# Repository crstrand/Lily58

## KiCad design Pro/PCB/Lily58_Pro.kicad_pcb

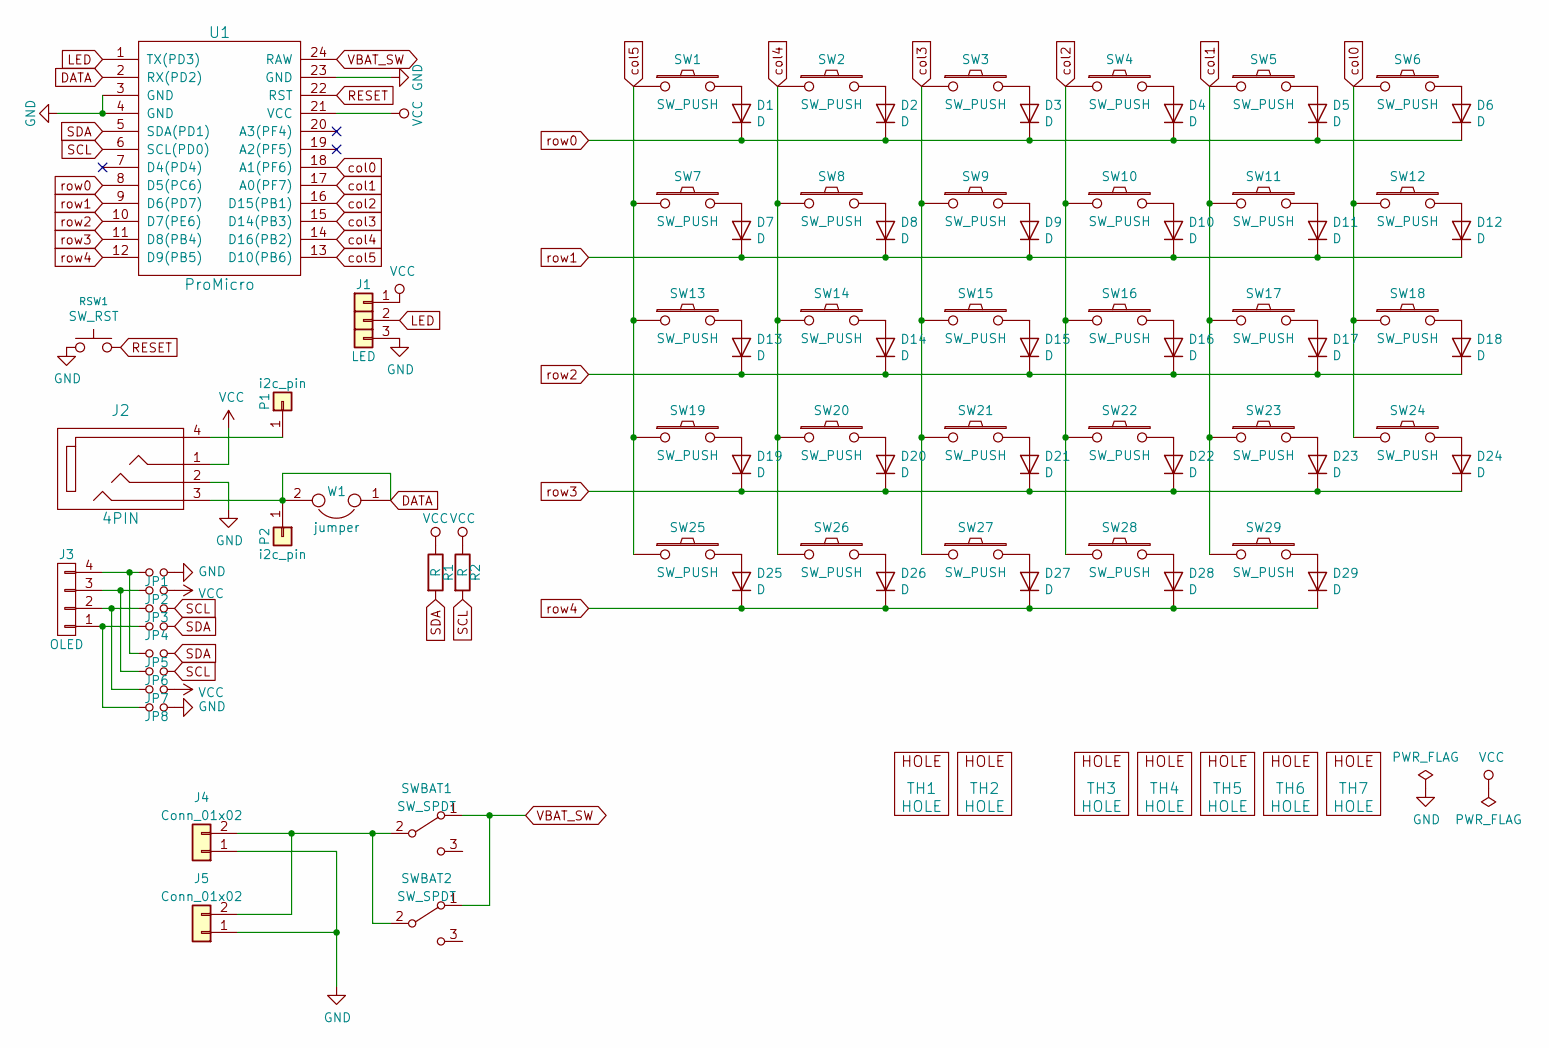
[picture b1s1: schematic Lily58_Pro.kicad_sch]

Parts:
D1, D2, D3, D4, D5, D6, D7, D8, D9, D10, D11, D12, D13, D14, D15, D16, D17, D18, D19, D20, D21, D22, D23, D24, D25, D26, D27, D28, D29: D; Diode_SOD123
J1: LED
J2: 4PIN; MJ-4PP-9
J3: OLED; OLED_4Pin
J4, J5: Conn_01x02; JST_PH_B2B-PH-K_1x02_P2.00mm_Vertical
JP1, JP2, JP3, JP4, JP5, JP6, JP7, JP8: Jumper_NO_Small; Jumper
P1, P2: i2c_pin; 1pin_conn
R1, R2: R; RESISTOR_mini
RSW1: SW_RST; TACT_SWITCH_TVBP06
SW1, SW2, SW3, SW4, SW5, SW6, SW7, SW8, SW9, SW10, SW11, SW12, SW13, SW14, SW15, SW16, SW17, SW18, SW19, SW20, SW21, SW22, SW23, SW24, SW25, SW26, SW27, SW28, SW29: SW_PUSH; MX_Choc_Hotswap
SWBAT1, SWBAT2: SW_SPDT; SW_SPDT_PCM12
TH1, TH2: HOLE; M2_HOLE_PCB
TH3, TH4, TH5, TH6, TH7: HOLE; HOLE_M2_TH
U1: ProMicro; ProMicro_rev2
W1: jumper; jumper_data

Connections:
GND: J1.3, J2.2, J4.1, J5.1, JP1.2, JP8.2, RSW1.1, U1.3 (GND), U1.4 (GND), U1.23 (GND)
LED: J1.2, U1.1 (TX(PD3))
unnamed: D1.2 (A), SW1.2
unnamed: D2.2 (A), SW2.2
unnamed: D3.2 (A), SW3.2
unnamed: D4.2 (A), SW4.2
unnamed: D5.2 (A), SW5.2
unnamed: D6.2 (A), SW6.2
unnamed: D7.2 (A), SW7.2
unnamed: D8.2 (A), SW8.2
unnamed: D9.2 (A), SW9.2
unnamed: D10.2 (A), SW10.2
unnamed: D11.2 (A), SW11.2
unnamed: D12.2 (A), SW12.2
unnamed: D13.2 (A), SW13.2
unnamed: D14.2 (A), SW14.2
unnamed: D15.2 (A), SW15.2
unnamed: D16.2 (A), SW16.2
unnamed: D17.2 (A), SW17.2
unnamed: D18.2 (A), SW18.2
unnamed: D19.2 (A), SW19.2
unnamed: D20.2 (A), SW20.2
unnamed: D21.2 (A), SW21.2
unnamed: D22.2 (A), SW22.2
unnamed: D23.2 (A), SW23.2
unnamed: D24.2 (A), SW24.2
unnamed: D25.2 (A), SW25.2
unnamed: D26.2 (A), SW26.2
unnamed: D27.2 (A), SW27.2
unnamed: D28.2 (A), SW28.2
unnamed: D29.2 (A), SW29.2
unnamed: J3.1, JP4.1, JP8.1
unnamed: J3.2, JP3.1, JP7.1
unnamed: J3.3, JP2.1, JP6.1
unnamed: J3.4, JP1.1, JP5.1
unnamed: J4.2, J5.2, SWBAT1.2 (B), SWBAT2.2 (B)
unnamed: J2.4, P1.1
RESET: RSW1.2, U1.22 (RST)
SCL: JP3.2, JP6.2, R2.2, U1.6 (SCL(PD0))
SDA: JP4.2, JP5.2, R1.2, U1.5 (SDA(PD1))
VBAT_SW: SWBAT1.1 (A), SWBAT2.1 (A), U1.24 (RAW)
VCC: J1.1, J2.1, JP2.2, JP7.2, R1.1, R2.1, U1.21 (VCC)
col0: SW6.1, SW12.1, SW18.1, SW24.1, U1.18 (A1(PF6))
col1: SW5.1, SW11.1, SW17.1, SW23.1, SW29.1, U1.17 (A0(PF7))
col2: SW4.1, SW10.1, SW16.1, SW22.1, SW28.1, U1.16 (D15(PB1))
col3: SW3.1, SW9.1, SW15.1, SW21.1, SW27.1, U1.15 (D14(PB3))
col4: SW2.1, SW8.1, SW14.1, SW20.1, SW26.1, U1.14 (D16(PB2))
col5: SW1.1, SW7.1, SW13.1, SW19.1, SW25.1, U1.13 (D10(PB6))
row0: D1.1 (K), D2.1 (K), D3.1 (K), D4.1 (K), D5.1 (K), D6.1 (K), U1.8 (D5(PC6))
row1: D7.1 (K), D8.1 (K), D9.1 (K), D10.1 (K), D11.1 (K), D12.1 (K), U1.9 (D6(PD7))
row2: D13.1 (K), D14.1 (K), D15.1 (K), D16.1 (K), D17.1 (K), D18.1 (K), U1.10 (D7(PE6))
row3: D19.1 (K), D20.1 (K), D21.1 (K), D22.1 (K), D23.1 (K), D24.1 (K), U1.11 (D8(PB4))
row4: D25.1 (K), D26.1 (K), D27.1 (K), D28.1 (K), D29.1 (K), U1.12 (D9(PB5))

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
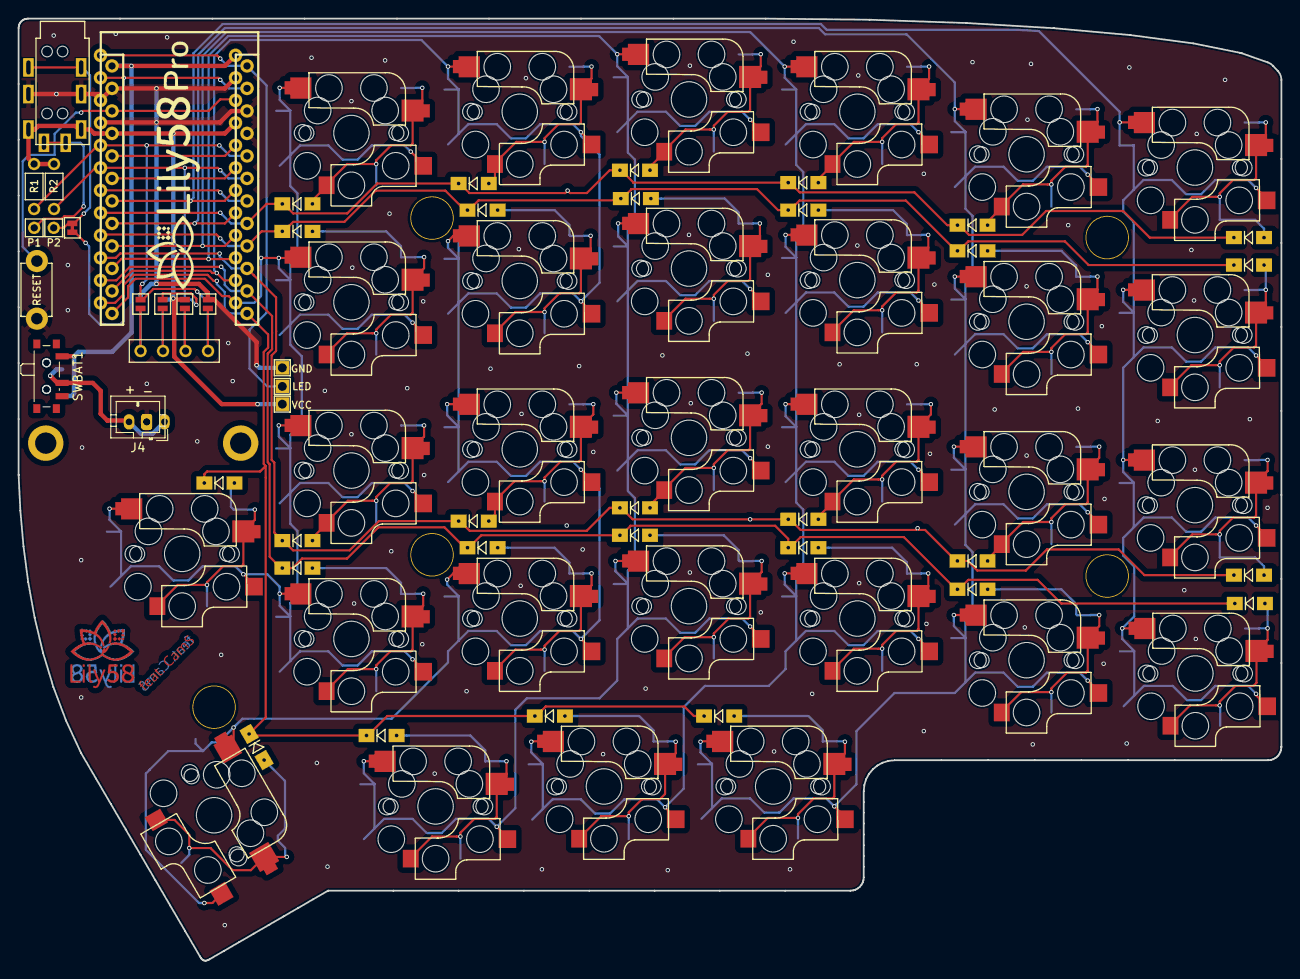
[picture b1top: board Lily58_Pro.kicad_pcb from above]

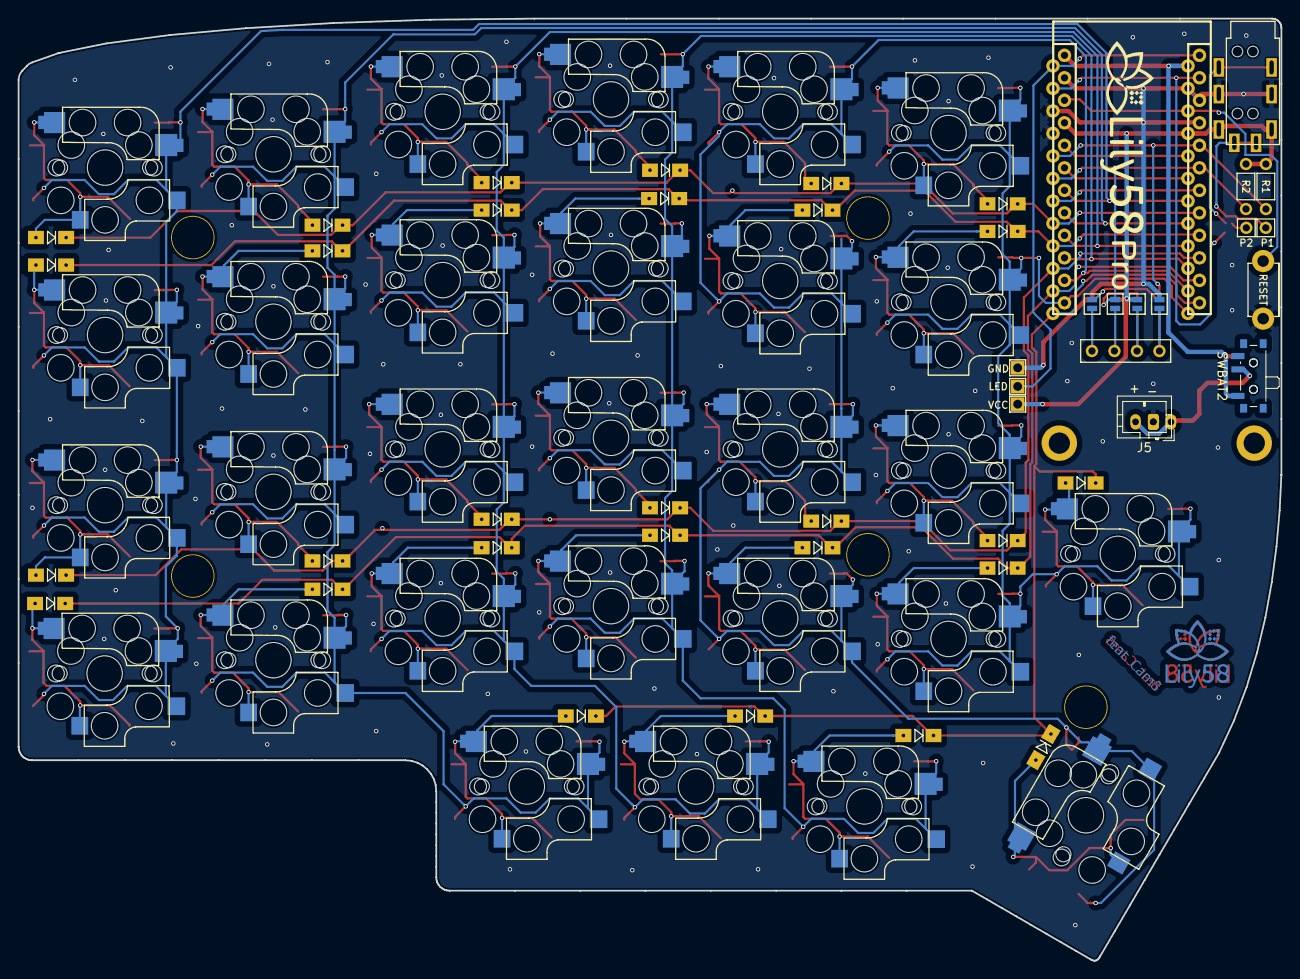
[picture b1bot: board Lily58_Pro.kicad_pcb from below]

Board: 2 copper layers, 142.5 x 106.3 mm, 87 parts (6 on the bottom side), 55 nets.

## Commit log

2023-09-16 Modified DRC rules to comply with JLCPCB.com capabilities. Added custom rule to ignore NPTH to soldermask errors. (version 1) (rule NPTH (constraint hole_clearance (min 0mm)) (constraint clearance (m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
2023-09-16 (re)Add library stuff
2023-09-16 Add more files for unknown reason to make git less mad at me
2023-09-16 expanded .gitignore
2023-09-16 Added two mounting hole to soldermask DRC error exceptions
2023-09-18 Exported STEP files for trial fit
2023-09-22 Added power switch and JST-PH 2.0 connector for battery. Flooded islands and via stitched top and bottom ground planes.
2023-09-22 Added "feat. CamS" as logo on copper layer
2023-11-05 Added connection from VBAT_SW to RAW pin on nano socket (for Nice!Nano)
2023-11-08 Minor cosmetic updates to PCB
2024-05-23 2mm fillet on upper right corner
2024-05-23 Saved with KiCad 8.0
2024-05-23 KiCad 8.0 as ordered 2024-05-22 20:50
